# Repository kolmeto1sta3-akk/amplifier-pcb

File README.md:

# Инструментальный усилитель на трёх ОУ

## 1. Назначение и схема

Плата — инструментальный усилитель на трёх операционных усилителях:

| Каскад | Элементы | Функция |
|---|---|---|
| Входной фильтр | R1, R2, C1–C3 | ФНЧ: подавление синфазных и дифференциальных ВЧ-помех |
| Входной каскад | DA1, DA2 (LT1222), R3–R5 | Неинвертирующие усилители с общим резистором R3 |
| Выходной каскад | DA3 (LT6202), R6–R9 | Дифференциальный усилитель, перевод в несимметричный выход |
| Блокировка питания | C4–C9 | По 0,1 мкФ на каждый вывод питания ОУ |
| Разъёмы | XT1 (вход), XT2 (питание ±3,3 В), XT3 (выход) | Разъёмы с шагом 1,25 мм |

**Коэффициент усиления:**

K = (1 + 2·R4 / R3) · (R8 / R6) = (1 + 2·2,2 кОм / 270 Ом) · 1 ≈ **17,3**

LT1222 устойчив при шумовом усилении ≥ 10; в первом каскаде оно ≈ 17,3.

**Входной фильтр:**
- дифференциальная полоса: f = 1 / (2π · 2R1 · (C2 + C1/2)) ≈ 1,0 кГц
- синфазная полоса: f = 1 / (2π · R1 · C1) ≈ 21 кГц
- C2 ≥ 10·C1 — разбаланс C1/C3 слабо влияет на подавление синфазного сигнала.

**Питание:** двуполярное ±3,3 В (6,6 В), в пределах допустимого для LT1222 (от 5 В) и LT6202 (до 12,6 В).

## 2. Структура репозитория

```
amplifier-pcb/
├── amplifier.kicad_pro      проект KiCad (классы цепей, правила)
├── amplifier.kicad_sch      схема электрическая принципиальная
├── amplifier.kicad_pcb      печатная плата
├── amplifier.kicad_dru      пользовательские правила DRC (нормы Резонит)
├── sym-lib-table            подключение библиотеки символов (относительный путь)
├── fp-lib-table             подключение библиотеки посадочных мест (относительный путь)
├── gost_portrait.kicad_wks  рамка и основная надпись по ГОСТ (А4, книжная)
├── gost_landscape.kicad_wks рамка по ГОСТ (альбомная)
├── library/                 git-сабмодуль → my-kicad-library
├── scripts/check.sh         ERC, DRC, Gerber, BOM, PDF
├── docs/                    скриншоты платы, PDF схемы
├── README.md
└── README.pdf               отчёт (PDF-версия этого файла)
```

Клонирование вместе с библиотекой:

```bash
git clone --recursive https://github.com/kolmeto1sta3-akk/amplifier-pcb.git
# если уже склонировано без --recursive:
git submodule update --init
```

## 3. Библиотека компонентов (git-сабмодуль)

Библиотека вынесена в отдельный репозиторий [my-kicad-library](https://github.com/kolmeto1sta3-akk/my-kicad-library) и подключена как сабмодуль в папку `library/`.

Пути подключения — **относительные**, через переменную `${KIPRJMOD}` (папка проекта), поэтому проект открывается на любом компьютере без настройки:

| Таблица | Имя | Путь |
|---|---|---|
| `sym-lib-table` | MySymbols | `${KIPRJMOD}/library/symbols/MySymbols.kicad_sym` |
| `fp-lib-table` | MyFootprints | `${KIPRJMOD}/library/footprints/MyFootprints.pretty` |

**Состав библиотеки:**

| УГО | Поз. обозн. | Посадочное место | Партномер |
|---|---|---|---|
| LT1222 (ОУ) | DA | SOIC-8_3.9x4.9mm_P1.27mm | LT1222CS8#PBF |
| LT6202 (ОУ) | DA | SOT-23-5 | LT6202CS5#TRMPBF |
| R (резистор) | R | R_0805_2012Metric | по номиналу |
| C (конденсатор) | C | C_0805_2012Metric | по номиналу |
| A1251WR-S-2P_IN / _OUT | XT | Molex_PicoBlade_53048-0210 (2 конт.) | A1251WR-S-2P |
| A1251WR-S-3P_PWR | XT | Molex_PicoBlade_53048-0310 (3 конт.) | A1251WR-S-3P |

**Оформление УГО по ГОСТ:**
- ОУ — ГОСТ 2.759-82: основное поле со знаком «▷» и два дополнительных поля для меток выводов (входы и V− слева, выход и V+ справа), отделённые вертикальными линиями; инвертирующий вход обозначен кружком;
- резистор и конденсатор — ГОСТ 2.728-74;
- разъёмы — таблицей «Цепь / Конт.»;
- буквенные позиционные обозначения — ГОСТ 2.710-81 (DA, R, C, XT).

Площадки разъёмов PicoBlade расширены до 0,9 мм, чтобы поясок вокруг отверстия 0,5 мм был не меньше 0,2 мм (норма Резонита).

## 4. Схема электрическая принципиальная

- **Оформление.** Лист А4, рамка и основная надпись по ГОСТ 2.104 (`gost_portrait.kicad_wks`), обозначение документа с кодом **Э3**.
- **Поле `Manufacturer_Part_Number`.** Заведено у всех компонентов, партномера подобраны на [lcsc.com](https://www.lcsc.com).

**Классы цепей** («Файл → Параметры схемы → Классы цепей»), с цветовым обозначением:

| Класс | Цепи (шаблон) | Цвет | Ширина дорожки |
|---|---|---|---|
| Power + | `+3V3` | красный | 0,5 мм |
| Power − | `-3V3` | синий | 0,5 мм |
| GND | `GND` | чёрный | 0,5 мм |
| Analog_IN | `*IN+`, `*IN-` | зелёный | 0,25 мм |
| Analog_OUT | `*OUT` | фиолетовый | 0,25 мм |
| Analog_SIGNAL | `*OUT1`, `*OUT2`, `Net-(*` | жёлтый | 0,25 мм |

> Шаблоны начинаются со `*`: у локальной метки полное имя цепи содержит путь листа (`/IN+`), поэтому шаблон `IN+` без звёздочки не срабатывает.

Полная схема в векторном виде: [`docs/amplifier_schematic.pdf`](docs/amplifier_schematic.pdf).

**Перечень элементов (BOM)** — формируется скриптом из поля `Manufacturer_Part_Number`:

| Поз. обозначение | Номинал | Корпус | Партномер (Manufacturer_Part_Number) | Кол. |
|---|---|---|---|---|
| C1, C3 | 0,012 мкФ | 0805 | CL21B123KBANNNC (Samsung) | 2 |
| C2 | 0,12 мкФ | 0805 | C0805C124K1RACTU (KEMET) | 1 |
| C4–C9 | 0,1 мкФ | 0805 | CL21B104KBFNNNE (Samsung) | 6 |
| DA1, DA2 | LT1222CS8 | SOIC-8 | LT1222CS8#PBF (Analog Devices) | 2 |
| DA3 | LT6202CS5 | SOT-23-5 | LT6202CS5#TRMPBF (Analog Devices) | 1 |
| R1, R2 | 620 Ом | 0805 | RC0805FR-07620RL (Yageo) | 2 |
| R3 | 270 Ом | 0805 | RC0805FR-07270RL (Yageo) | 1 |
| R4–R9 | 2,2 кОм | 0805 | RC0805FR-072K2L (Yageo) | 6 |
| XT1, XT3 | вилка 2 конт. | шаг 1,25 мм | A1251WR-S-2P (CJT) | 2 |
| XT2 | вилка 3 конт. | шаг 1,25 мм | A1251WR-S-3P (CJT) | 1 |

**Результат ERC:** 0 нарушений.

## 5. Печатная плата и технологичность (DFMA)

Нормы завода «Резонит», базовый уровень, фольга 35 мкм ([источник](https://www.rezonit.ru/pcb/odnostoronnie-i-dvustoronnie/serial/)):

| Параметр | Резонит | В проекте |
|---|---|---|
| Ширина проводника / зазор | ≥ 0,2 / 0,2 мм | 0,25 (сигнал), 0,5 (питание) / 0,2 мм |
| Мин. металлизированное отверстие | 0,3 мм | 0,3 мм |
| Поясок площадки (PAD) | 0,2 мм | 0,2 мм (правило в `.kicad_dru`) |
| Поясок переходного отверстия | 0,15 мм | 0,15 мм |
| Медь от края платы | 0,25 мм | 0,5 мм |
| Шелкография: линия / высота шрифта | 0,15 / 1,0 мм | 0,15 / 1,0 мм |

**Решения DFMA:**
- двусторонняя плата FR-4 1,6 мм, все компоненты на верхней стороне — один проход монтажа;
- единый типоразмер пассивных компонентов 0805 — удобно и для ручной, и для автоматической пайки;
- компоненты ориентированы только под 0° / 90°, разъёмы у края платы;
- сплошной полигон GND на нижнем слое, блокировочные конденсаторы рядом с выводами питания;
- входные цепи IN+ / IN− разведены симметрично;
- позиционные обозначения на шелкографии читаемы и не заходят на площадки.

**Трассировка:**
- плата 50 × 35 мм, 2 слоя, 124 сегмента дорожек, 12 переходных отверстий;
- сигнальные цепи — 0,25 мм, питание ±3,3 В и GND — 0,5 мм;
- изломы дорожек только под 45° (угол 135°): острых и прямых углов нет, выходы из площадок — прямые или под 45°;
- все сигнальные цепи и питание — на верхнем слое; на нижний слой выведены только два участка +3V3, чтобы пересечь другие цепи;
- нижний слой — сплошной полигон GND; верхний слой залит GND, островки полигона верхнего слоя сшиты с нижним переходными отверстиями GND (0,8/0,4 мм);
- контакты GND разъёмов XT2, XT3 подключены к полигонам сплошным соединением (термобарьер не помещается между контактами с шагом 1,25 мм).

**Результат проверки DRC:** 0 нарушений, 0 неразведённых соединений, 0 расхождений со схемой.

## 6. Скрипт проверки и выпуска документации

`scripts/check.sh` (macOS / Linux) последовательно выполняет:

1. **ERC** — проверка схемы (`output/erc.rpt`), при ошибках скрипт останавливается;
2. **DRC** — проверка платы и её соответствия схеме (`output/drc.rpt`);
3. **Gerber + Excellon** — `output/gerbers/`, архив `amplifier_gerbers.zip` для заказа в Резоните;
4. **BOM** — перечень элементов с партномерами `output/amplifier_BOM.csv`;
5. **PDF схемы** — `output/amplifier_schematic.pdf`.

Запуск:

```bash
./scripts/check.sh
```

Используется `kicad-cli` из состава KiCad 10.

Результат последнего запуска:

```
=== 1/5 ERC ===  Найдено 0 нарушений
=== 2/5 DRC ===  Найдено 0 нарушений, 0 неподключенных элементов, 0 проблем с соответствием схеме
=== 3/5 Gerber + сверловка ===  F_Cu, B_Cu, F_Paste, F/B_Silkscreen, F/B_Mask, Edge_Cuts, amplifier.drl
=== 4/5 BOM ===  output/amplifier_BOM.csv
=== 5/5 PDF схемы ===  output/amplifier_schematic.pdf
```

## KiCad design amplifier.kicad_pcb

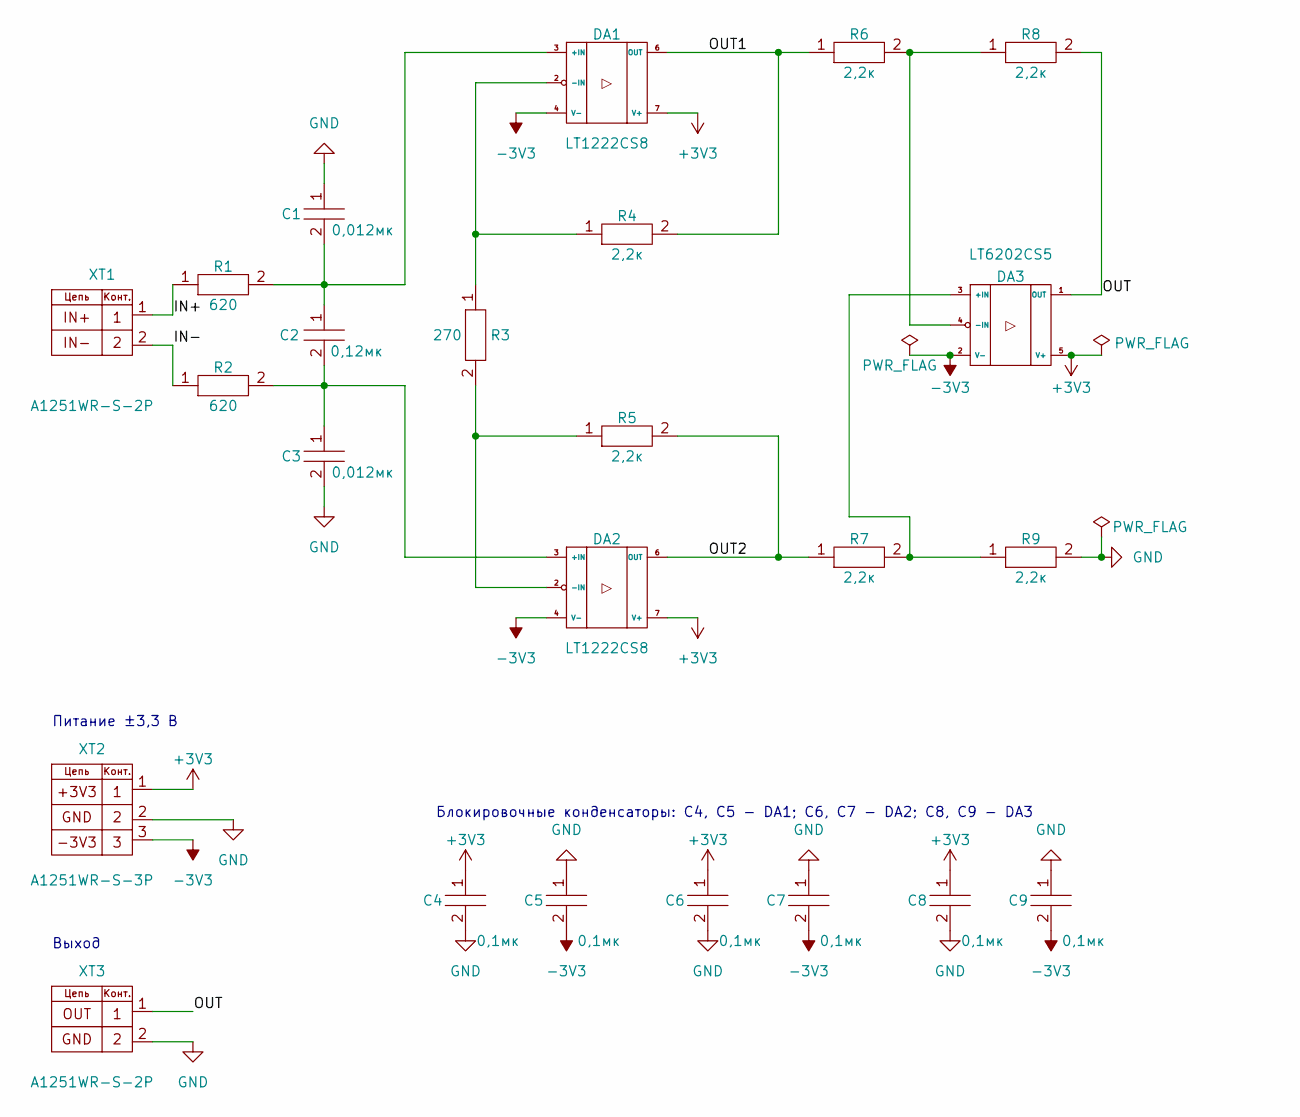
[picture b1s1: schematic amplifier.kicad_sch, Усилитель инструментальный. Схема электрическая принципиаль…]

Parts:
C1, C3: 0,012мк; C_0805_2012Metric; Manufacturer_Part_Number CL21B123KBANNNC
C2: 0,12мк; C_0805_2012Metric; Manufacturer_Part_Number C0805C124K1RACTU
C4, C5, C6, C7, C8, C9: 0,1мк; C_0805_2012Metric; Manufacturer_Part_Number CL21B104KBFNNNE
DA1, DA2: LT1222CS8; SOIC-8_3.9x4.9mm_P1.27mm; Manufacturer_Part_Number LT1222CS8#PBF
DA3: LT6202CS5; SOT-23-5; Manufacturer_Part_Number LT6202CS5#TRMPBF
R1, R2: 620; R_0805_2012Metric; Manufacturer_Part_Number RC0805FR-07620RL
R3: 270; R_0805_2012Metric; Manufacturer_Part_Number RC0805FR-07270RL
R4, R5, R6, R7, R8, R9: 2,2к; R_0805_2012Metric; Manufacturer_Part_Number RC0805FR-072K2L
XT1, XT3: A1251WR-S-2P; Molex_PicoBlade_53048-0210_1x02_P1.25mm_Horizontal; Manufacturer_Part_Number A1251WR-S-2P
XT2: A1251WR-S-3P; Molex_PicoBlade_53048-0310_1x03_P1.25mm_Horizontal; Manufacturer_Part_Number A1251WR-S-3P

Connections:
+3V3: C4.1, C6.1, C8.1, DA1.7 (V+), DA2.7 (V+), DA3.5 (V+), XT2.1
-3V3: C5.2, C7.2, C9.2, DA1.4 (V-), DA2.4 (V-), DA3.2 (V-), XT2.3
/IN+: R1.1, XT1.1
/IN-: R2.1, XT1.2
/OUT: DA3.1 (OUT), R8.2, XT3.1
/OUT1: DA1.6 (OUT), R4.2, R6.1
/OUT2: DA2.6 (OUT), R5.2, R7.1
GND: C1.1, C3.2, C4.2, C5.1, C6.2, C7.1, C8.2, C9.1, R9.2, XT2.2, XT3.2
unnamed: C1.2, C2.1, DA1.3 (+IN), R1.2
unnamed: DA1.2 (-IN), R3.1, R4.1
unnamed: C2.2, C3.1, DA2.3 (+IN), R2.2
unnamed: DA2.2 (-IN), R3.2, R5.1
unnamed: DA3.3 (+IN), R7.2, R9.1
unnamed: DA3.4 (-IN), R6.2, R8.1

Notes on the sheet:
Питание ±3,3 В
Выход
Блокировочные конденсаторы: C4, C5 - DA1; C6, C7 - DA2; C8, C9 - DA3

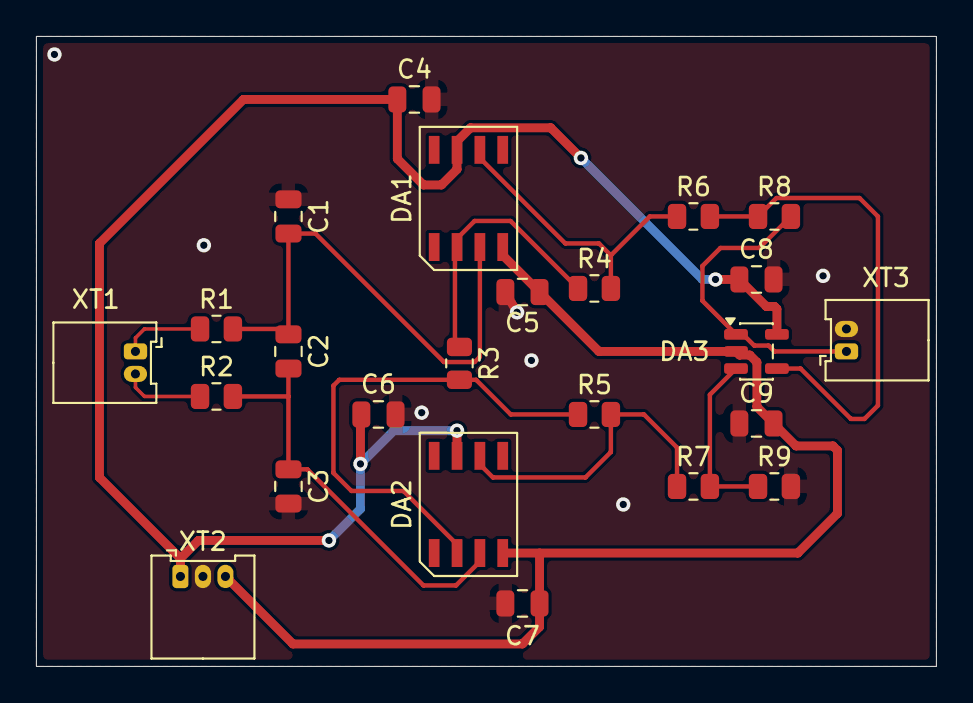
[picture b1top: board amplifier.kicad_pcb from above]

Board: 2 copper layers, 50.0 x 35.0 mm, 24 parts (0 on the bottom side), 14 nets.
